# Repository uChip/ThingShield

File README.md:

# ThingShield
The [SparkFun Thing (WRL-13231)](https://www.sparkfun.com/products/13231) is a board for creating Internet of Things devices based on the ESP-8266 WiFi microcontroller.  This repo contains "shield" designs in the form factor and pinout of the Thing.

ThingShield_Bare is a set (schematic and board) of design files that have the basic board outline and pinout.  Use this as the start of your own shield design.  I have left a voltage regulator circuit on the board for power.  The regulator is easily deleted if it does not meet your needs.

ThingShield_Proto is a board with prototyping area.  Again there is a voltage regulator on the shield board.  The regulator can be omitted if your design does not need much current.  Instead you can draw power directly from the Thing board.

Bare circuit boards of the proto shield can be ordered from [OSH Park](https://oshpark.com/shared_projects/OK6ncANs)

Boards propogate the CC license of the parent SparkFun board.  No liability accepted.

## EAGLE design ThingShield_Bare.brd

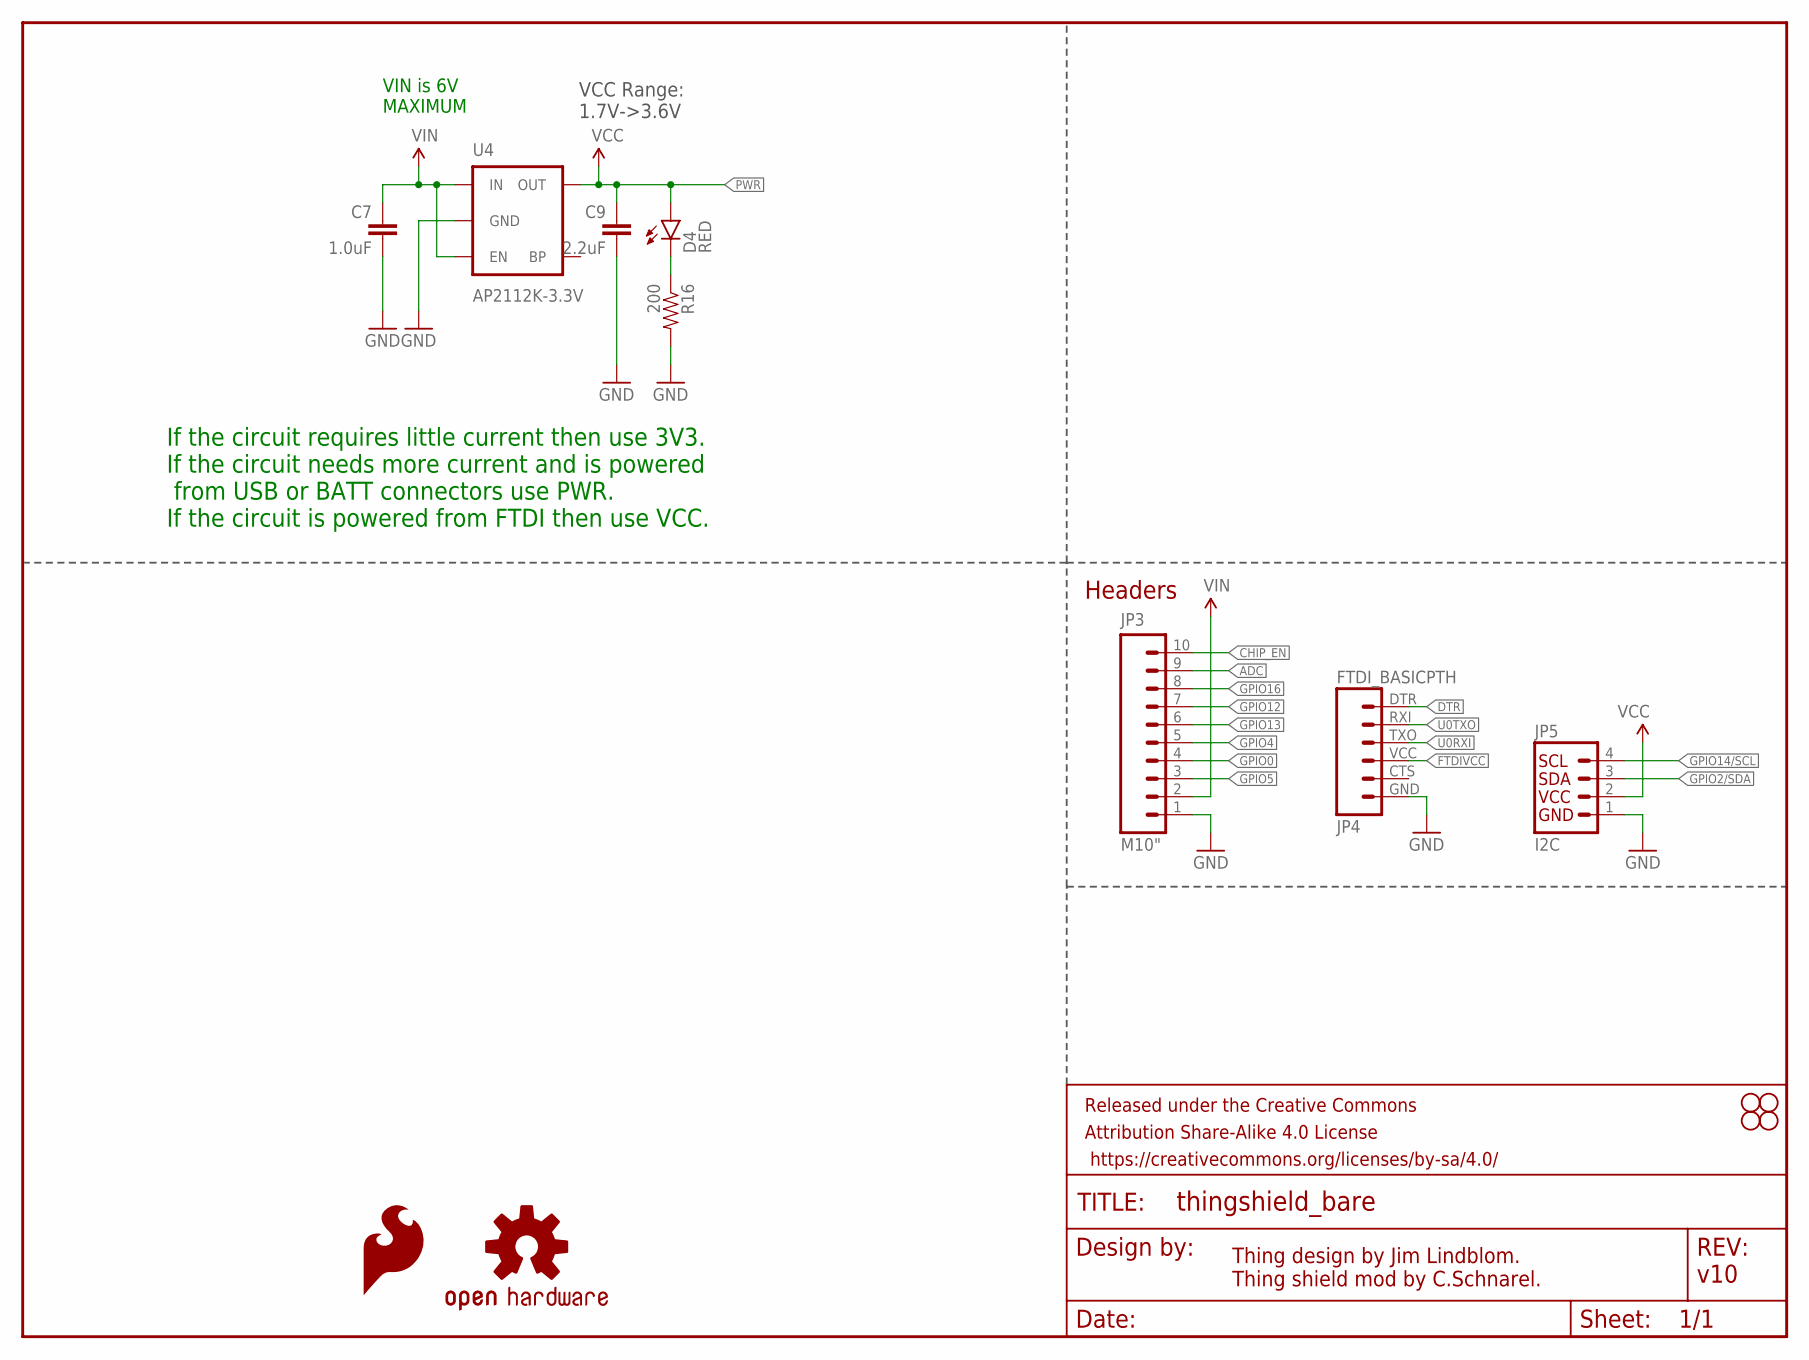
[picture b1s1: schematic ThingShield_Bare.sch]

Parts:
C7: 1.0uF; 0805
C9: 2.2uF; 0603-CAP
D4: RED; LED-0603
FRAME1: FRAME-LETTER; CREATIVE_COMMONS
JP3: M10"; 1X10
JP4: FTDI_BASICPTH; FTDI_BASIC
JP5: I2C; 1X04
LOGO3: SFE_LOGO_FLAME.1_INCH; SFE_LOGO_FLAME_.1
LOGO4: OSHW-LOGOS; OSHW-LOGO-S
R16: 200; 0603-RES
STANDOFF1, STANDOFF2, STANDOFF3, STANDOFF4: STAND-OFF
U4: AP2112K-3.3V; SOT23-5

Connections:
ADC: JP3.9
CHIP_EN: JP3.10
DTR: JP4.DTR (1)
FTDIVCC: JP4.VCC (4)
GND: C7.2, C9.2, JP3.1, JP4.GND (6), JP5.1, R16.2, U4.2 (GND)
GPIO0: JP3.4
GPIO2/SDA: JP5.3
GPIO4: JP3.5
GPIO5: JP3.3
GPIO12: JP3.7
GPIO13: JP3.6
GPIO14/SCL: JP5.4
GPIO16: JP3.8
unnamed: D4.C, R16.1
PWR: C9.1, D4.A, U4.5 (OUT)
U0RXI: JP4.TXO (3)
U0TXO: JP4.RXI (2)
VCC: JP5.2
VIN: C7.1, JP3.2, U4.1 (IN), U4.3 (EN)

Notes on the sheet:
Thing design by Jim Lindblom. Thing shield mod by C.Schnarel.
Headers
v10
VCC Range: 1.7V->3.6V
If the circuit requires little current then use 3V3. If the circuit needs more current and is powered from USB or BATT connectors use PWR. If the circuit is powered from FTDI then use VCC.
VIN is 6V MAXIMUM

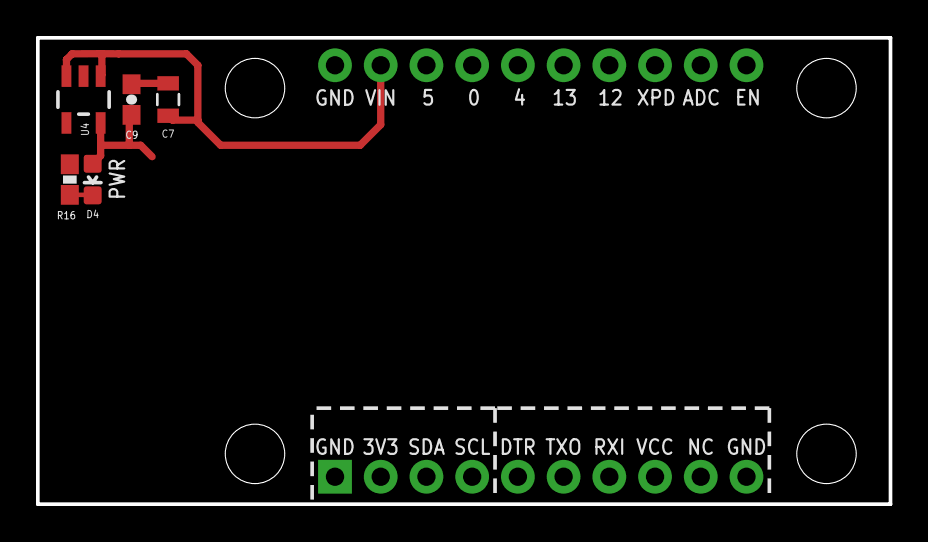
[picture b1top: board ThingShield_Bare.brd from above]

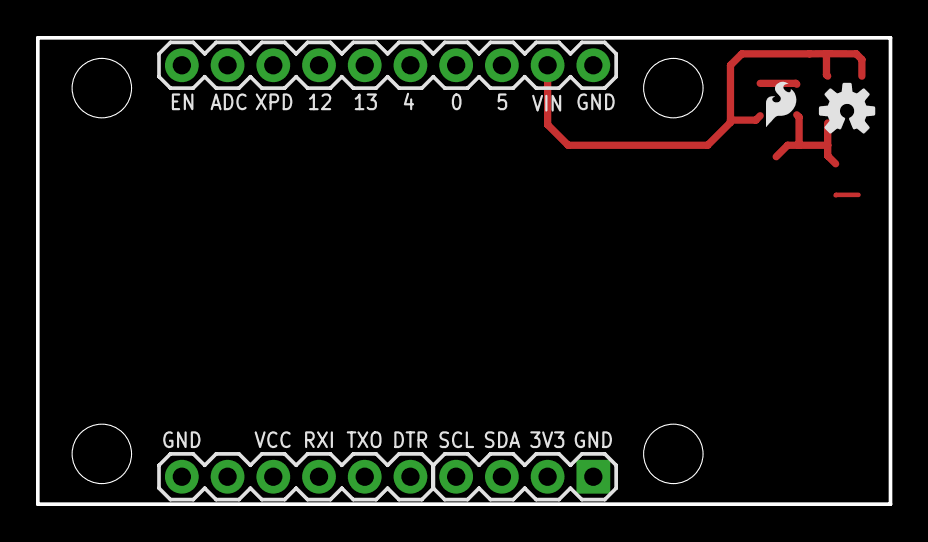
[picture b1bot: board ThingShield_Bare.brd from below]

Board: 2 copper layers, 47.4 x 25.9 mm, 15 parts (5 on the bottom side), 4 nets.

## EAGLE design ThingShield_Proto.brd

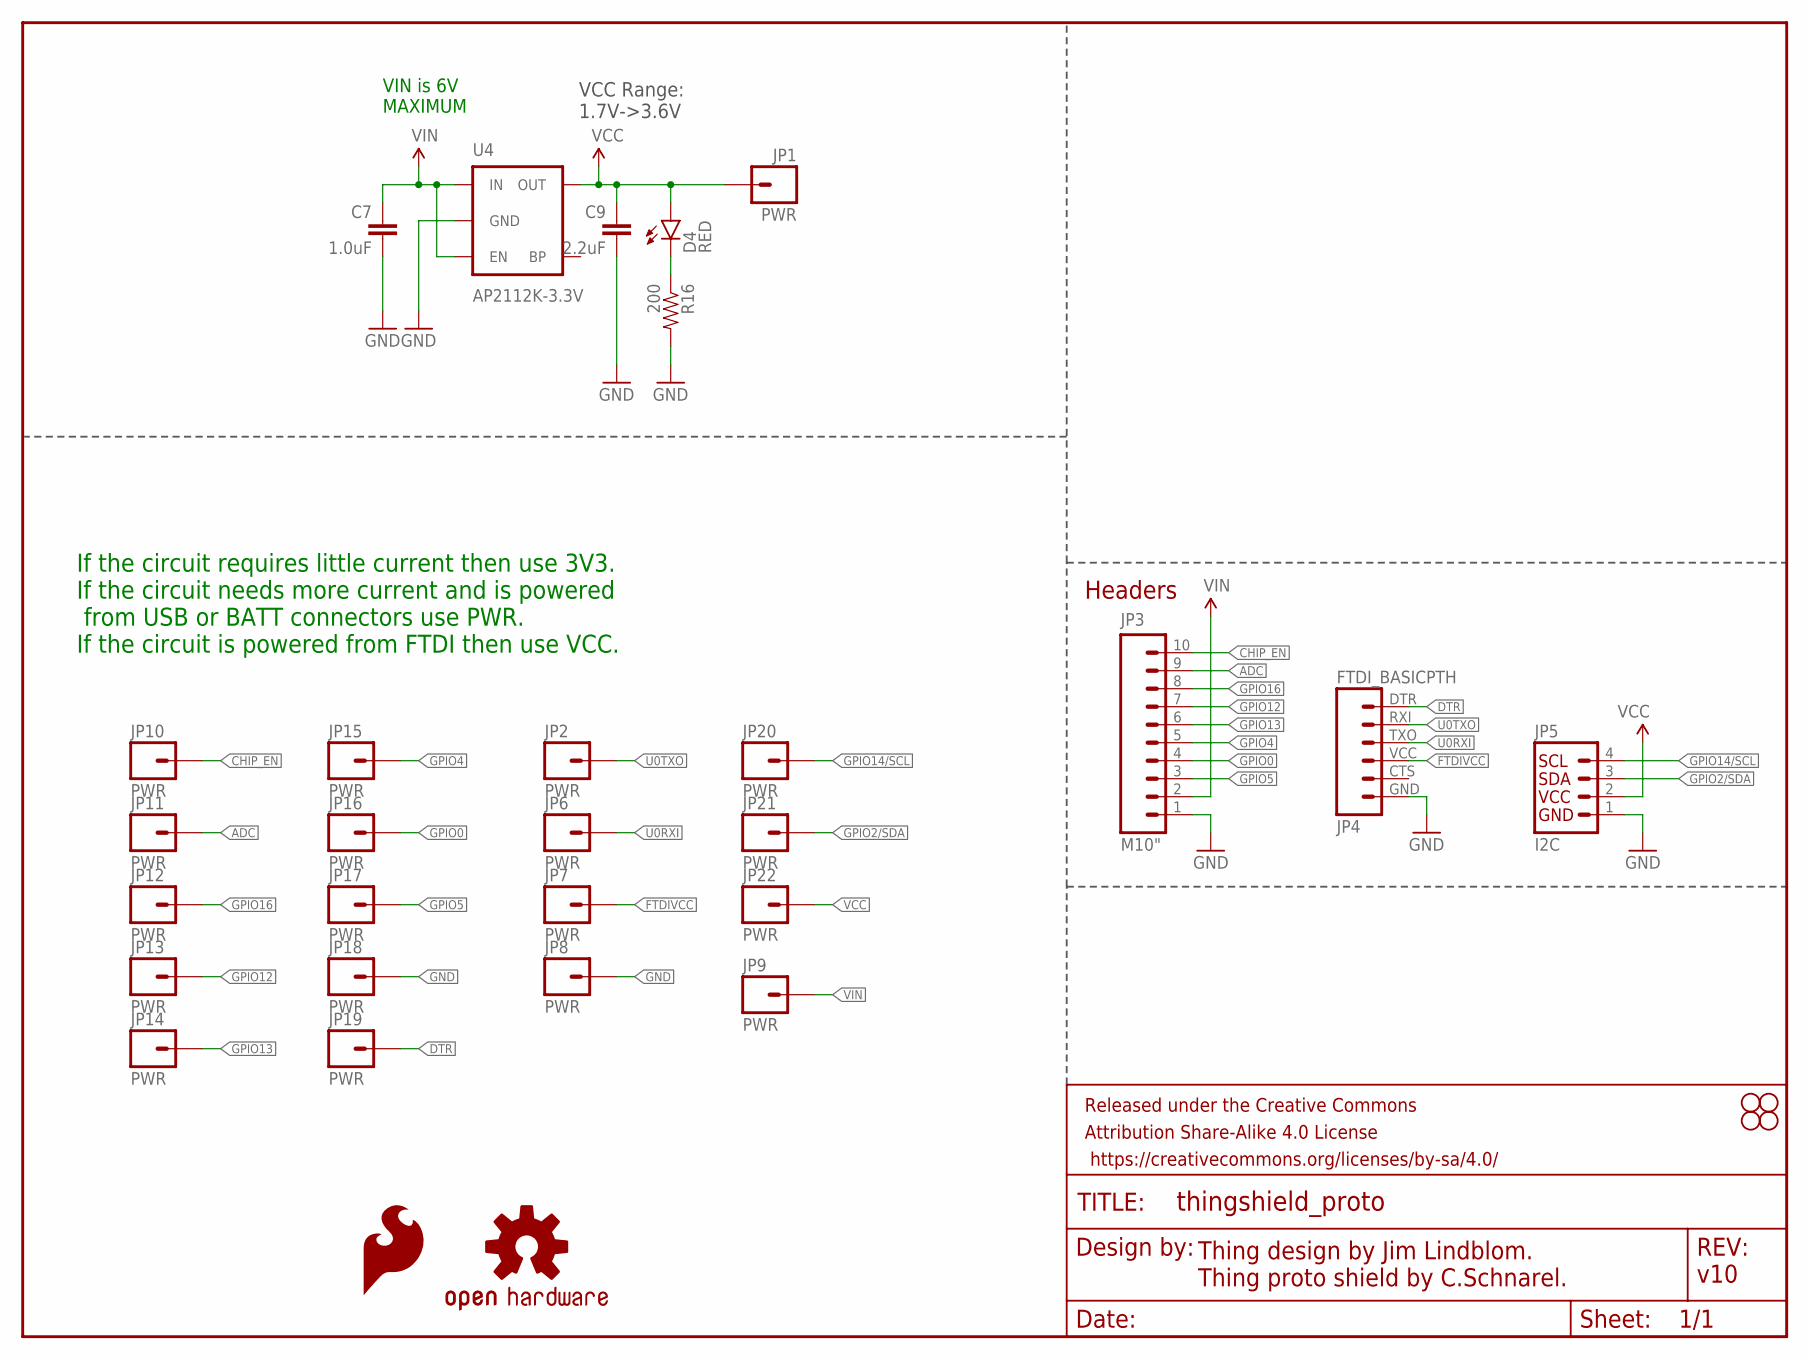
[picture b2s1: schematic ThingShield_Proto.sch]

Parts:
C7: 1.0uF; 0805
C9: 2.2uF; 0603-CAP
D4: RED; LED-0603
FRAME1: FRAME-LETTER; CREATIVE_COMMONS
JP1, JP2, JP6, JP7, JP8, JP9, JP10, JP11, JP12, JP13, JP14, JP15, JP16, JP17, JP18, JP19, JP20, JP21, JP22: PWR; 1X01
JP3: M10"; 1X10
JP4: FTDI_BASICPTH; FTDI_BASIC
JP5: I2C; 1X04
LOGO3: SFE_LOGO_FLAME.1_INCH; SFE_LOGO_FLAME_.1
LOGO4: OSHW-LOGOS; OSHW-LOGO-S
R16: 200; 0603-RES
STANDOFF1, STANDOFF2, STANDOFF3, STANDOFF4: STAND-OFF
U4: AP2112K-3.3V; SOT23-5

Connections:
ADC: JP3.9, JP11.1
CHIP_EN: JP3.10, JP10.1
DTR: JP4.DTR (1), JP19.1
FTDIVCC: JP4.VCC (4), JP7.1
GND: C7.2, C9.2, JP3.1, JP4.GND (6), JP5.1, JP8.1, JP18.1, R16.2, U4.2 (GND)
GPIO0: JP3.4, JP16.1
GPIO2/SDA: JP5.3, JP21.1
GPIO4: JP3.5, JP15.1
GPIO5: JP3.3, JP17.1
GPIO12: JP3.7, JP13.1
GPIO13: JP3.6, JP14.1
GPIO14/SCL: JP5.4, JP20.1
GPIO16: JP3.8, JP12.1
unnamed: D4.C, R16.1
PWR: C9.1, D4.A, JP1.1, U4.5 (OUT)
U0RXI: JP4.TXO (3), JP6.1
U0TXO: JP2.1, JP4.RXI (2)
VCC: JP5.2, JP22.1
VIN: C7.1, JP3.2, JP9.1, U4.1 (IN), U4.3 (EN)

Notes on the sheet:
Thing design by Jim Lindblom. Thing proto shield by C.Schnarel.
Headers
v10
VCC Range: 1.7V->3.6V
If the circuit requires little current then use 3V3. If the circuit needs more current and is powered from USB or BATT connectors use PWR. If the circuit is powered from FTDI then use VCC.
VIN is 6V MAXIMUM

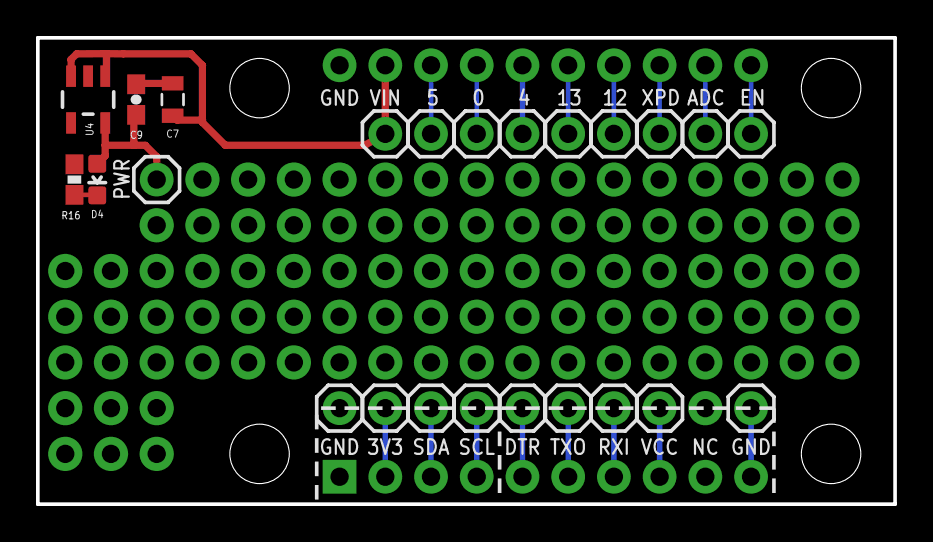
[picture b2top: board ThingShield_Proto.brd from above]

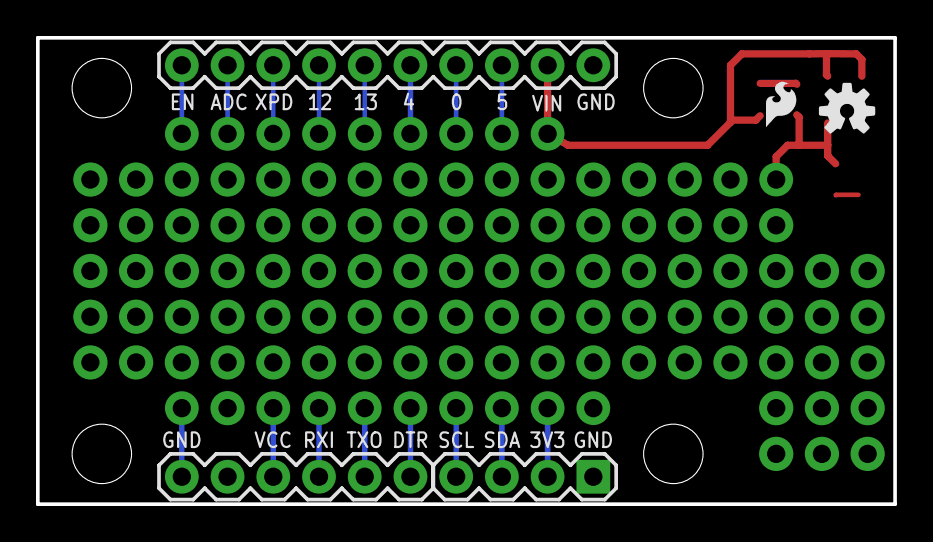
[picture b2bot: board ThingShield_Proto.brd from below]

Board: 2 copper layers, 47.6 x 25.9 mm, 34 parts (5 on the bottom side), 19 nets.

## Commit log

2015-05-23 :tada: Added .gitattributes & .gitignore files
2015-05-23 Shield boards for SF Thing
    Bare board design in Eagle.
    Proto shield design in Eagle.
2015-05-23 Create README.md
    First cut at README.
2015-05-23 Added link to image in README
2015-05-23 README edits
2015-05-23 First cut at module as a component
    NOT YET TESTED!
2015-05-23 Component edits

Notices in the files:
parts and their libraries:
SparkFun-Capacitors: Licensing: Creative Commons ShareAlike 4.0 International - https://creativecommons.org/licenses/by-sa/4.0
SparkFun-Aesthetics: Released under the Creative Commons Attribution Share-Alike 4.0 License
SparkFun-Aesthetics: https://creativecommons.org/licenses/by-sa/4.0
